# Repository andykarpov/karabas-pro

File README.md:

# Karabas-Pro

**Yet another FPGA ZX Spectrum clone ;)**

## Intro

ZX Spectrum compatible machine with a soft CPU, FDD and HDD (CF card) controllers, PS/2 keyboard/mouse, ESP8266 UART, RTC, VGA output and all logic inside the Altera FPGA **EP4CE10**.

## The idea

The idea was to make a smaller Profi (Профи) ZX Spectrum clone, with real FDD and HDD controllers. The board size fits the dimensions of the real 3.5" floppy drive. 

## Firmwares

**The main firmware is finished and currently it implements:**

1) ZX Spectrum classic and profi hi-res hi-color mode (with palette) (512x240)
2) ZX Profi CMR ports for extended peripherial
3) FDD controller that works both in CP/M and classic modes
4) HDD controller (works in Profi CP/M mode and PQ-DOS mode)
5) PS/2 keyboard (XT keyboard emulation)
6) PS/2 mouse (kempston mouse and serial MS mouse emulation)
7) VGA output (requires a monitor with 50Hz support)
8) Turbosound (2 x AY-3-8912), Soundrive and SAA1099 (SAA will work only on EP4CE10 due to lack of free LEs in EP4CE6)
9) Kempston joystick support
10) SEGA joystick support
11) RTC (profi), emulated read/write support
12) SD card access via Z-Controller emulation as well as DivMMC
13) Turbo 7 MHz (nowait) and Turbo 14 Mhz (with wait cycles)
14) ZX UNO simple UART @115200 for ESP8266 module, ZiFi API support (a secondary ZX UNO UART available on uBus connector for EP4CE10)
15) An additional ROM bank with **PQ-DOS BIOS**
16) An additional ROM bank with **Flash Tool** by **Doctor Max** to upgrade the FGPA firmware and ROM banks without programmer
17) An additional ROM bank with **FDImage Tool** by **Doctor Max** to extract TRD, SCL, PRO, TD0 and FDI images on real floppies
18) OSD menu
19) OSD full-screen overlay with easy-to-change options, RTC setup, etc.

## More info

**ERRATA for PCB rev.A:** [See ERRATA Rev.A](https://github.com/andykarpov/karabas-pro/blob/master/ERRATA-REVA.md).

**ERRATA for PCB rev.B:** [See ERRATA Rev.B](https://github.com/andykarpov/karabas-pro/blob/master/ERRATA-REVB.md).

**ERRATA for PCB rev.С:** [See ERRATA Rev.С](https://github.com/andykarpov/karabas-pro/blob/master/ERRATA-REVC.md).

**Latest stable revision:** rev.Ї.

**PCB changelog:** [PCB changelog](https://github.com/andykarpov/karabas-pro/blob/master/CHANGELOG-PCB.md).

**Profi firmware** [Download a Profi firmware](https://github.com/andykarpov/karabas-pro/tree/master/firmware/releases/profi).

**Donations** [See DONATIONS.md](https://github.com/andykarpov/karabas-pro/blob/master/DONATIONS.md).

## Development & Building

### AVR Firmware
The ATmega328P supervisor firmware is built using [PlatformIO](https://platformio.org/):

```bash
cd firmware/src/avr
pio run
```

This compiles the universal firmware, generates all revision-specific `.eep` files, and automatically syncs them to `firmware/releases/`.

To automatically rebuild and stage updated firmware binaries whenever you commit AVR changes, install the git hooks:
```bash
./scripts/install-hooks.sh
```

### Pre-production renders:

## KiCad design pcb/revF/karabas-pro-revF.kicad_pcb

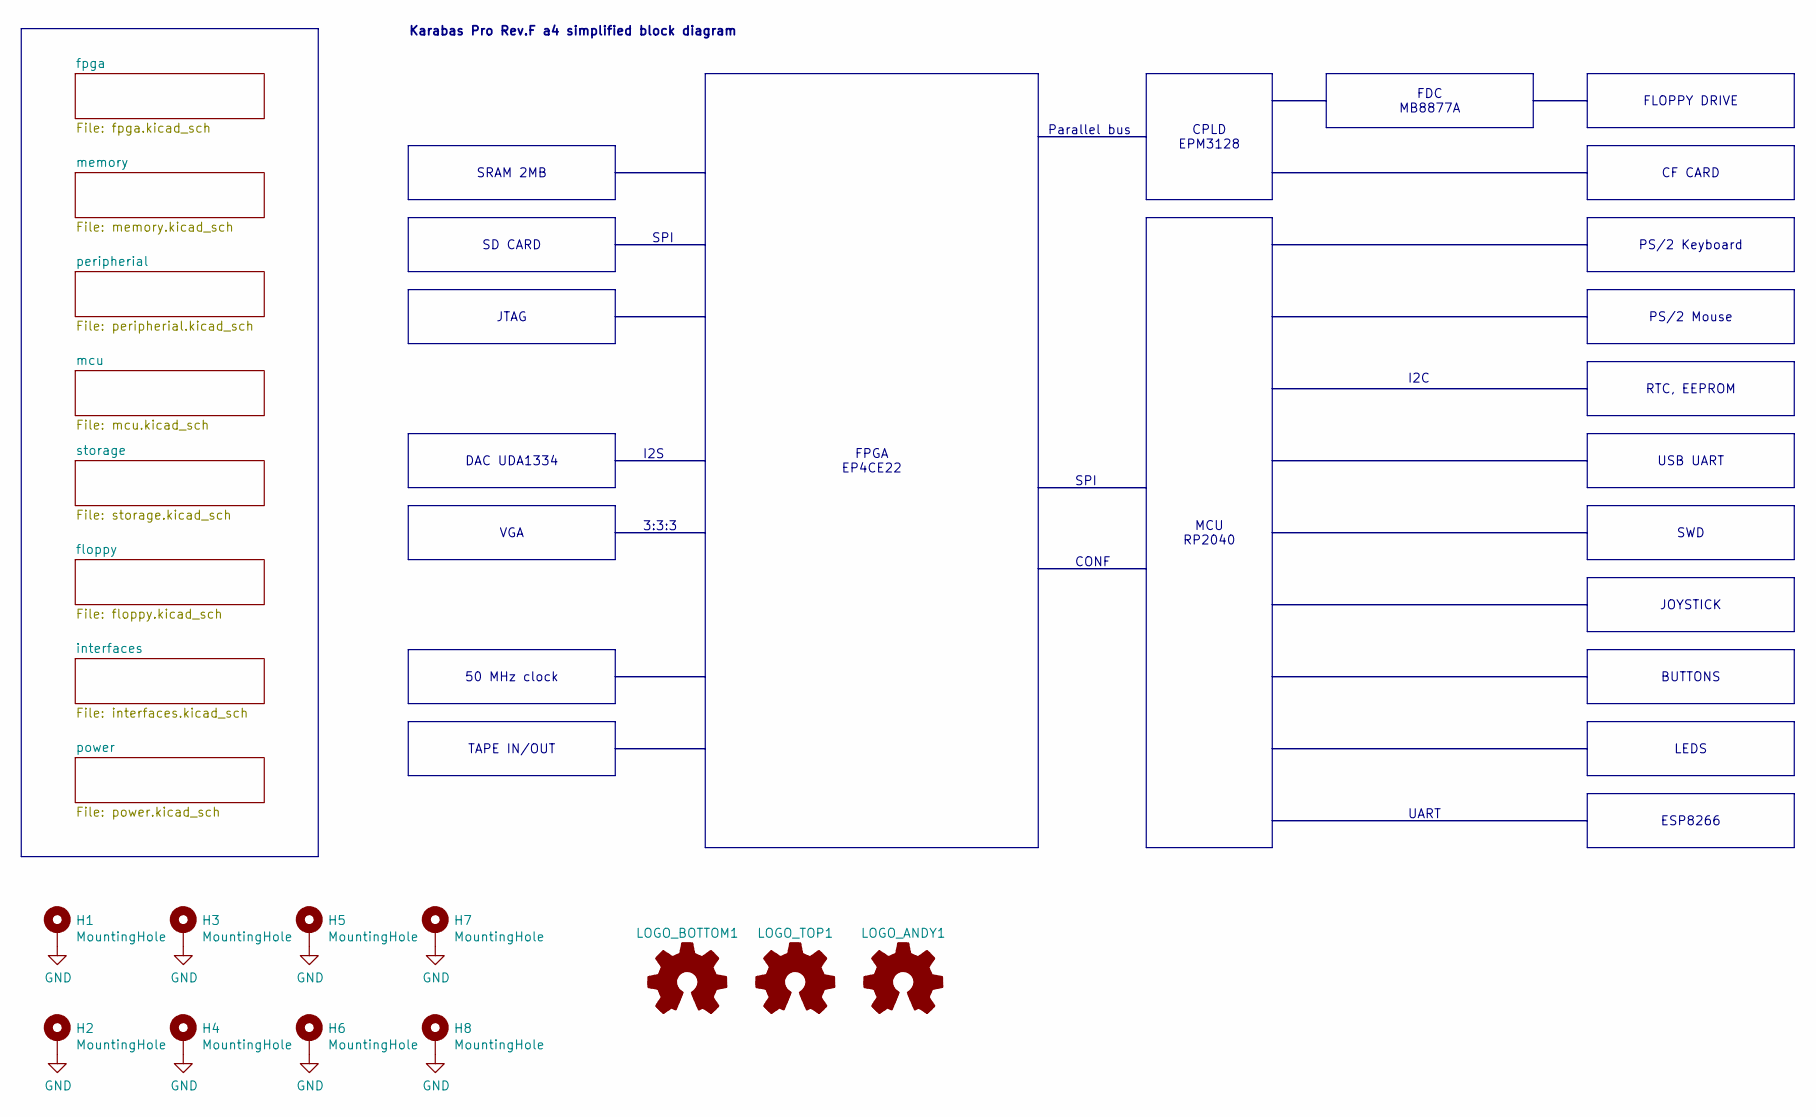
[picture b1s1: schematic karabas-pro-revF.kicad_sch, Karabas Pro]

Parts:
H1, H2, H3, H4, H5, H6, H7, H8: MountingHole; MountingHole_3.5mm_Pad_Via
LOGO_ANDY1: Logo_Open_Hardware_Small; andy_karpov_logo4_silk
LOGO_BOTTOM1: Logo_Open_Hardware_Small; karabas_pro_logo4_copper
LOGO_TOP1: Logo_Open_Hardware_Small; karabas_pro_logo4_copper

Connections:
GND: H1.1, H2.1, H3.1, H4.1, H5.1, H6.1, H7.1, H8.1; also elsewhere on the board

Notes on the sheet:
I2S
I2C
Parallel bus
3:3:3
Karabas Pro Rev.${REVISION} simplified block diagram
UART
SPI
CONF
PS/2 Keyboard
FDC MB8877A
CPLD EPM3128
50 MHz clock
JTAG
RTC, EEPROM
ESP8266
BUTTONS
PS/2 Mouse
USB UART
JOYSTICK
SWD
CF CARD
VGA
SD CARD
TAPE IN/OUT
SRAM 2MB
LEDS
FLOPPY DRIVE
FPGA EP4CE22
DAC UDA1334
MCU RP2040

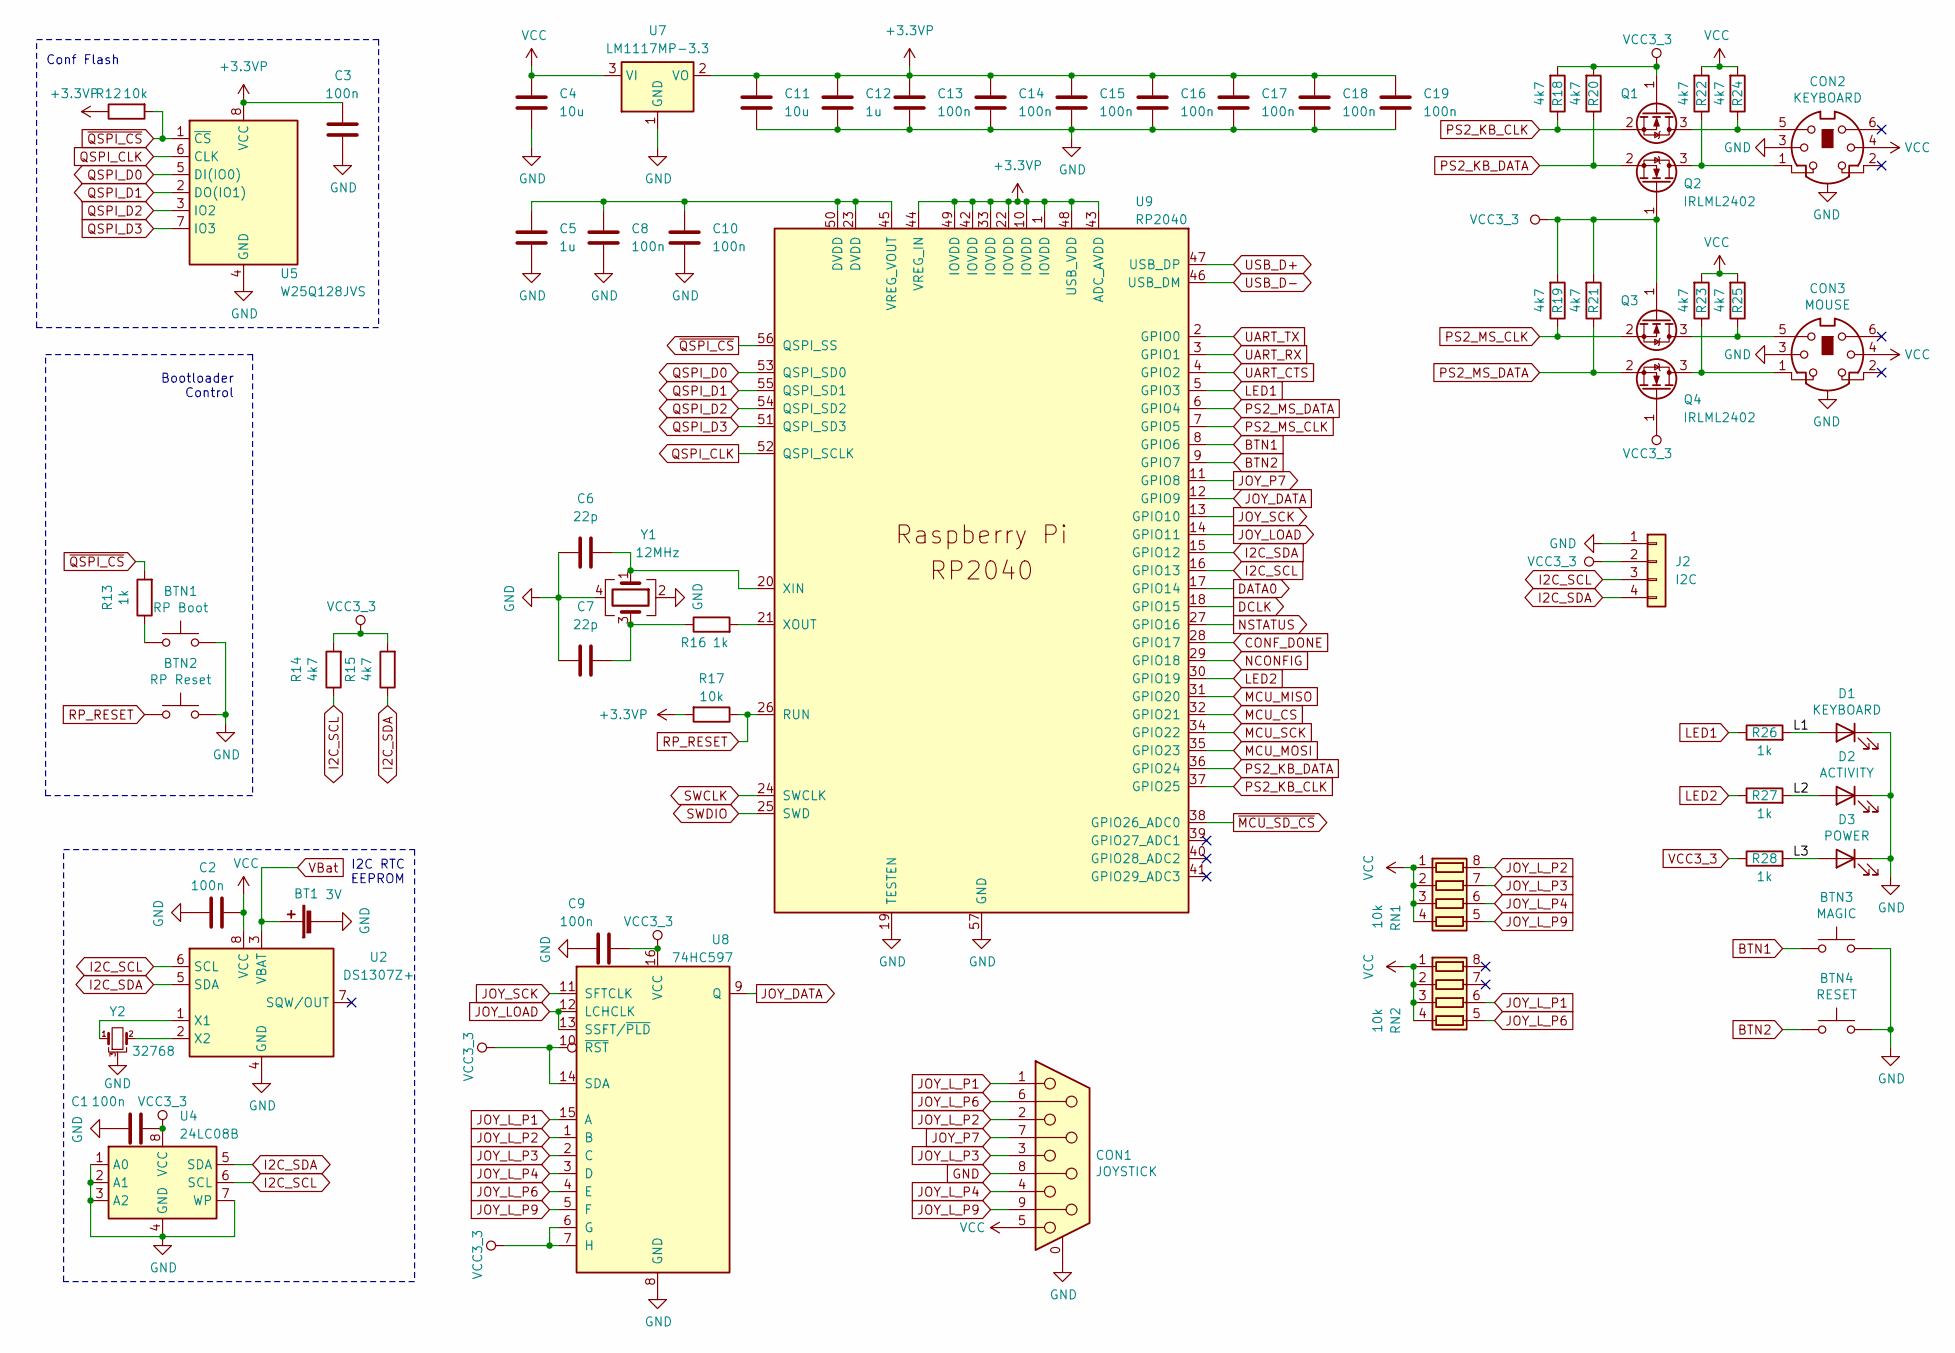
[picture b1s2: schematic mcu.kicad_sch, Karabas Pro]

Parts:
BT1: 3V; BAT_BS-7-BLUE
BTN1: RP Boot; SW_SPST_PTS810_handsoldering
BTN2: RP Reset; SW_SPST_PTS810_handsoldering
BTN3: MAGIC; SW_Tactile_SPST_Angled_PTS645Vx58-2LFS
BTN4: RESET; SW_Tactile_SPST_Angled_PTS645Vx58-2LFS
C1, C2, C3, C8, C9, C10, C13, C14, C15, C16, C17, C18, C19: 100n; C_0805_2012Metric_Pad1.18x1.45mm_HandSolder
C4, C11: 10u; C_0805_2012Metric_Pad1.18x1.45mm_HandSolder
C5, C12: 1u; C_0805_2012Metric_Pad1.18x1.45mm_HandSolder
C6, C7: 22p; C_0805_2012Metric_Pad1.18x1.45mm_HandSolder
CON1: JOYSTICK; DSUB-9_Pins_Horizontal_P2.77x2.84mm_EdgePinOffset7.70mm_Hou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
CON2: KEYBOARD; MINI_DIN_6_33PRIMARY
CON3: MOUSE; MINI_DIN_6_33PRIMARY
D1: KEYBOARD; LED_0805_2012Metric_Pad1.15x1.40mm_HandSolder
D2: ACTIVITY; LED_0805_2012Metric_Pad1.15x1.40mm_HandSolder
D3: POWER; LED_0805_2012Metric_Pad1.15x1.40mm_HandSolder
J2: I2C; PinHeader_1x04_P2.54mm_Vertical
Q1, Q2, Q3, Q4: IRLML2402; SOT-23_Handsoldering
R12, R17: 10k; R_0805_2012Metric_Pad1.20x1.40mm_HandSolder
R13, R16, R26, R27, R28: 1k; R_0805_2012Metric_Pad1.20x1.40mm_HandSolder
R14, R15, R18, R19, R20, R21, R22, R23, R24, R25: 4k7; R_0805_2012Metric_Pad1.20x1.40mm_HandSolder
RN1, RN2: 10k; R_Array_Convex_4x0603
U2: DS1307Z+; SOIC-8_3.9x4.9mm_P1.27mm
U4: 24LC08B; SO-8_3.9x4.9mm_P1.27mm
U5: W25Q128JVS; SOIC-8_5.23x5.23mm_P1.27mm-LONG
U7: LM1117MP-3.3; SOT-223-3_TabPin2
U8: 74HC597; SO-16_3.9x9.9mm_P1.27mm
U9: RP2040; QFN-56-1EP_7x7mm_P0.4mm_EP3.2x3.2mm_ThermalViaBig
Y1: 12MHz; Crystal_SMD_3225-4Pin_3.2x2.5mm_HandSoldering
Y2: 32768; Crystal_C26-LF_D2.1mm_L6.5mm_Horizontal_1EP_style2

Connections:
+3.3VP: C3.2, C11.1, C12.1, C13.1, C14.1, C15.1, C16.1, C17.1, C18.1, C19.1, R12.1, R17.2, U5.8 (VCC), U7.2 (VO), U9.1 (IOVDD), U9.10 (IOVDD), U9.22 (IOVDD), U9.33 (IOVDD), U9.42 (IOVDD), U9.43 (ADC_AVDD), U9.44 (VREG_IN), U9.48 (USB_VDD), U9.49 (IOVDD)
/mcu/L1: D1.2 (A), R26.2
/mcu/L2: D2.2 (A), R27.2
/mcu/L3: D3.2 (A), R28.2
BTN1: BTN3.1, U9.8 (GPIO6)
BTN2: BTN4.1, U9.9 (GPIO7)
CONF_DONE: U9.28 (GPIO17); also elsewhere on the board
DATA0: U9.17 (GPIO14); also elsewhere on the board
DCLK: U9.18 (GPIO15); also elsewhere on the board
GND: BT1.2 (-), BTN1.2, BTN2.2, BTN3.2, BTN4.2, C1.2, C2.2, C3.1, C4.2, C5.2, C6.2, C7.2, C8.2, C9.2, C10.2, C11.2, C12.2, C13.2, C14.2, C15.2, C16.2, C17.2, C18.2, C19.2, CON1.0 (PAD), CON1.8, CON2.3, CON2.GND, CON3.3, CON3.GND, D1.1 (K), D2.1 (K), D3.1 (K), J2.1, U2.4 (GND), U4.1 (A0), U4.2 (A1), U4.3 (A2), U4.4 (GND), U4.7 (WP), U5.4 (GND), U7.1 (GND), U8.8 (GND), U9.19 (TESTEN), U9.57 (GND), Y1.2, Y1.4, Y2.3; also elsewhere on the board
I2C_SCL: J2.3, R14.1, U2.6 (SCL), U4.6 (SCL), U9.16 (GPIO13)
I2C_SDA: J2.4, R15.1, U2.5 (SDA), U4.5 (SDA), U9.15 (GPIO12)
JOY_DATA: U8.9 (Q), U9.12 (GPIO9)
JOY_LOAD: U8.12 (LCHCLK), U8.13 (SSFT/~PLD), U9.14 (GPIO11)
JOY_L_P1: CON1.1, RN2.6 (R3.2), U8.15 (A)
JOY_L_P2: CON1.2, RN1.8 (R1.2), U8.1 (B)
JOY_L_P3: CON1.3, RN1.7 (R2.2), U8.2 (C)
JOY_L_P4: CON1.4, RN1.6 (R3.2), U8.3 (D)
JOY_L_P6: CON1.6, RN2.5 (R4.2), U8.4 (E)
JOY_L_P9: CON1.9, RN1.5 (R4.2), U8.5 (F)
JOY_P7: CON1.7, U9.11 (GPIO8)
JOY_SCK: U8.11 (SFTCLK), U9.13 (GPIO10)
LED1: R26.1, U9.5 (GPIO3)
LED2: R27.1, U9.30 (GPIO19)
MCU_CS: U9.32 (GPIO21); also elsewhere on the board
MCU_MISO: U9.31 (GPIO20); also elsewhere on the board
MCU_MOSI: U9.35 (GPIO23); also elsewhere on the board
MCU_SCK: U9.34 (GPIO22); also elsewhere on the board
NCONFIG: U9.29 (GPIO18); also elsewhere on the board
NSTATUS: U9.27 (GPIO16); also elsewhere on the board
unnamed: BTN1.1, R13.1
unnamed: C7.1, R16.1, Y1.3
unnamed: CON2.5, Q1.3 (D), R24.1
unnamed: CON2.1, Q2.3 (D), R22.1
unnamed: CON3.5, Q3.3 (D), R25.1
unnamed: CON3.1, Q4.3 (D), R23.1
unnamed: U2.1 (X1), Y2.1
unnamed: U2.2 (X2), Y2.2
unnamed: C5.1, C8.1, C10.1, U9.23 (DVDD), U9.45 (VREG_VOUT), U9.50 (DVDD)
unnamed: C6.1, U9.20 (XIN), Y1.1
unnamed: R16.2, U9.21 (XOUT)
PS2_KB_CLK: Q1.2 (S), R18.1, U9.37 (GPIO25)
PS2_KB_DATA: Q2.2 (S), R20.1, U9.36 (GPIO24)
PS2_MS_CLK: Q3.2 (S), R19.1, U9.7 (GPIO5)
PS2_MS_DATA: Q4.2 (S), R21.1, U9.6 (GPIO4)
QSPI_CLK: U5.6 (CLK), U9.52 (QSPI_SCLK)
QSPI_D0: U5.5 (DI(IO0)), U9.53 (QSPI_SD0)
QSPI_D1: U5.2 (DO(IO1)), U9.55 (QSPI_SD1)
QSPI_D2: U5.3 (IO2), U9.54 (QSPI_SD2)
QSPI_D3: U5.7 (IO3), U9.51 (QSPI_SD3)
RP_RESET: BTN2.1, R17.1, U9.26 (RUN)
SWCLK: U9.24 (SWCLK)
SWDIO: U9.25 (SWD)
UART_CTS: U9.4 (GPIO2); also elsewhere on the board
UART_RX: U9.3 (GPIO1); also elsewhere on the board
UART_TX: U9.2 (GPIO0); also elsewhere on the board
USB_D+: U9.47 (USB_DP); also elsewhere on the board
USB_D-: U9.46 (USB_DM); also elsewhere on the board
VBat: BT1.1 (+), U2.3 (VBAT)
VCC: C2.1, C4.1, CON1.5, CON2.4, CON3.4, R22.2, R23.2, R24.2, R25.2, RN1.1 (R1.1), RN1.2 (R2.1), RN1.3 (R3.1), RN1.4 (R4.1), RN2.1 (R1.1), RN2.2 (R2.1), RN2.3 (R3.1), RN2.4 (R4.1), U2.8 (VCC), U7.3 (VI); also elsewhere on the board
VCC3_3: C1.1, C9.1, J2.2, Q1.1 (G), Q2.1 (G), Q3.1 (G), Q4.1 (G), R14.2, R15.2, R18.2, R19.2, R20.2, R21.2, R28.1, U4.8 (VCC), U8.6 (G), U8.7 (H), U8.10 (~RST), U8.14 (SDA), U8.16 (VCC); also elsewhere on the board
~MCU_SD_CS: U9.38 (GPIO26_ADC0); also elsewhere on the board
~QSPI_CS: R12.2, R13.2, U5.1 (~CS), U9.56 (QSPI_SS)

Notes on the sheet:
I2C RTC EEPROM
Bootloader Control
Conf Flash

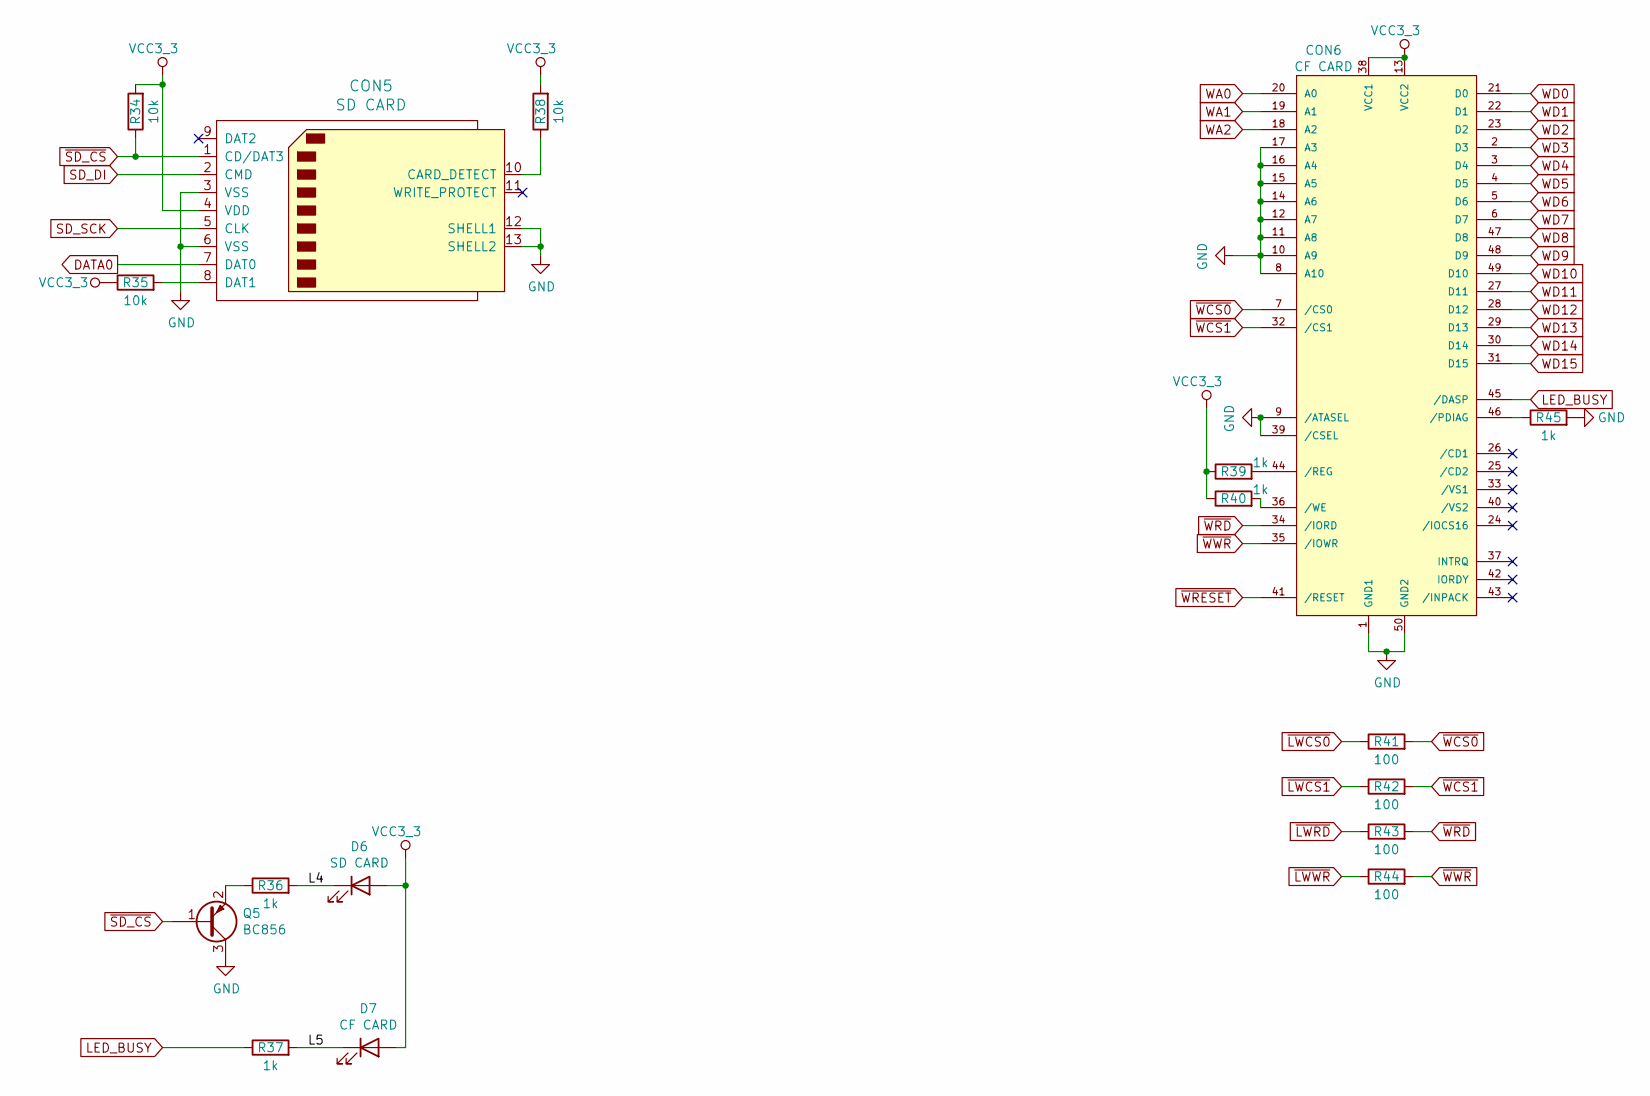
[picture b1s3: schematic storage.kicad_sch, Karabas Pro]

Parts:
CON5: SD CARD; SD_TE_2041021-mod
CON6: CF CARD; TE_1734451-1-LONG
D6: SD CARD; LED_0805_2012Metric_Pad1.15x1.40mm_HandSolder
D7: CF CARD; LED_0805_2012Metric_Pad1.15x1.40mm_HandSolder
Q5: BC856; SOT-23_Handsoldering
R34, R35, R38: 10k; R_0805_2012Metric_Pad1.20x1.40mm_HandSolder
R36, R37, R39, R40, R45: 1k; R_0805_2012Metric_Pad1.20x1.40mm_HandSolder
R41, R42, R43, R44: 100; R_0805_2012Metric_Pad1.20x1.40mm_HandSolder

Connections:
/storage/L4: D6.1 (K), R36.2
/storage/L5: D7.1 (K), R37.2
DATA0: CON5.7 (DAT0); also elsewhere on the board
GND: CON5.3 (VSS), CON5.6 (VSS), CON5.12 (SHELL1), CON5.13 (SHELL2), CON6.1 (GND1), CON6.8 (A10), CON6.9 (/ATASEL), CON6.10 (A9), CON6.11 (A8), CON6.12 (A7), CON6.14 (A6), CON6.15 (A5), CON6.16 (A4), CON6.17 (A3), CON6.39 (/CSEL), CON6.50 (GND2), Q5.3 (C), R45.2; also elsewhere on the board
LED_BUSY: CON6.45 (/DASP), R37.1
unnamed: CON5.10 (CARD_DETECT), R38.1
unnamed: CON5.8 (DAT1), R35.2
unnamed: CON6.46 (/PDIAG), R45.1
unnamed: CON6.44 (/REG), R39.2
unnamed: CON6.36 (/WE), R40.2
unnamed: Q5.2 (E), R36.1
SD_DI: CON5.2 (CMD); also elsewhere on the board
SD_SCK: CON5.5 (CLK); also elsewhere on the board
VCC3_3: CON5.4 (VDD), CON6.13 (VCC2), CON6.38 (VCC1), D6.2 (A), D7.2 (A), R34.2, R35.1, R38.2, R39.1, R40.1; also elsewhere on the board
WA0: CON6.20 (A0); also elsewhere on the board
WA1: CON6.19 (A1); also elsewhere on the board
WA2: CON6.18 (A2); also elsewhere on the board
WD0: CON6.21 (D0); also elsewhere on the board
WD1: CON6.22 (D1); also elsewhere on the board
WD2: CON6.23 (D2); also elsewhere on the board
WD3: CON6.2 (D3); also elsewhere on the board
WD4: CON6.3 (D4); also elsewhere on the board
WD5: CON6.4 (D5); also elsewhere on the board
WD6: CON6.5 (D6); also elsewhere on the board
WD7: CON6.6 (D7); also elsewhere on the board
WD8: CON6.47 (D8); also elsewhere on the board
WD9: CON6.48 (D9); also elsewhere on the board
WD10: CON6.49 (D10); also elsewhere on the board
WD11: CON6.27 (D11); also elsewhere on the board
WD12: CON6.28 (D12); also elsewhere on the board
WD13: CON6.29 (D13); also elsewhere on the board
WD14: CON6.30 (D14); also elsewhere on the board
WD15: CON6.31 (D15); also elsewhere on the board
~LWCS0: R41.1; also elsewhere on the board
~LWCS1: R42.1; also elsewhere on the board
~LWRD: R43.1; also elsewhere on the board
~LWWR: R44.1; also elsewhere on the board
~SD_CS: CON5.1 (CD/DAT3), Q5.1 (B), R34.1; also elsewhere on the board
~WCS0: CON6.7 (/CS0), R41.2
~WCS1: CON6.32 (/CS1), R42.2
~WRD: CON6.34 (/IORD), R43.2
~WRESET: CON6.41 (/RESET); also elsewhere on the board
~WWR: CON6.35 (/IOWR), R44.2

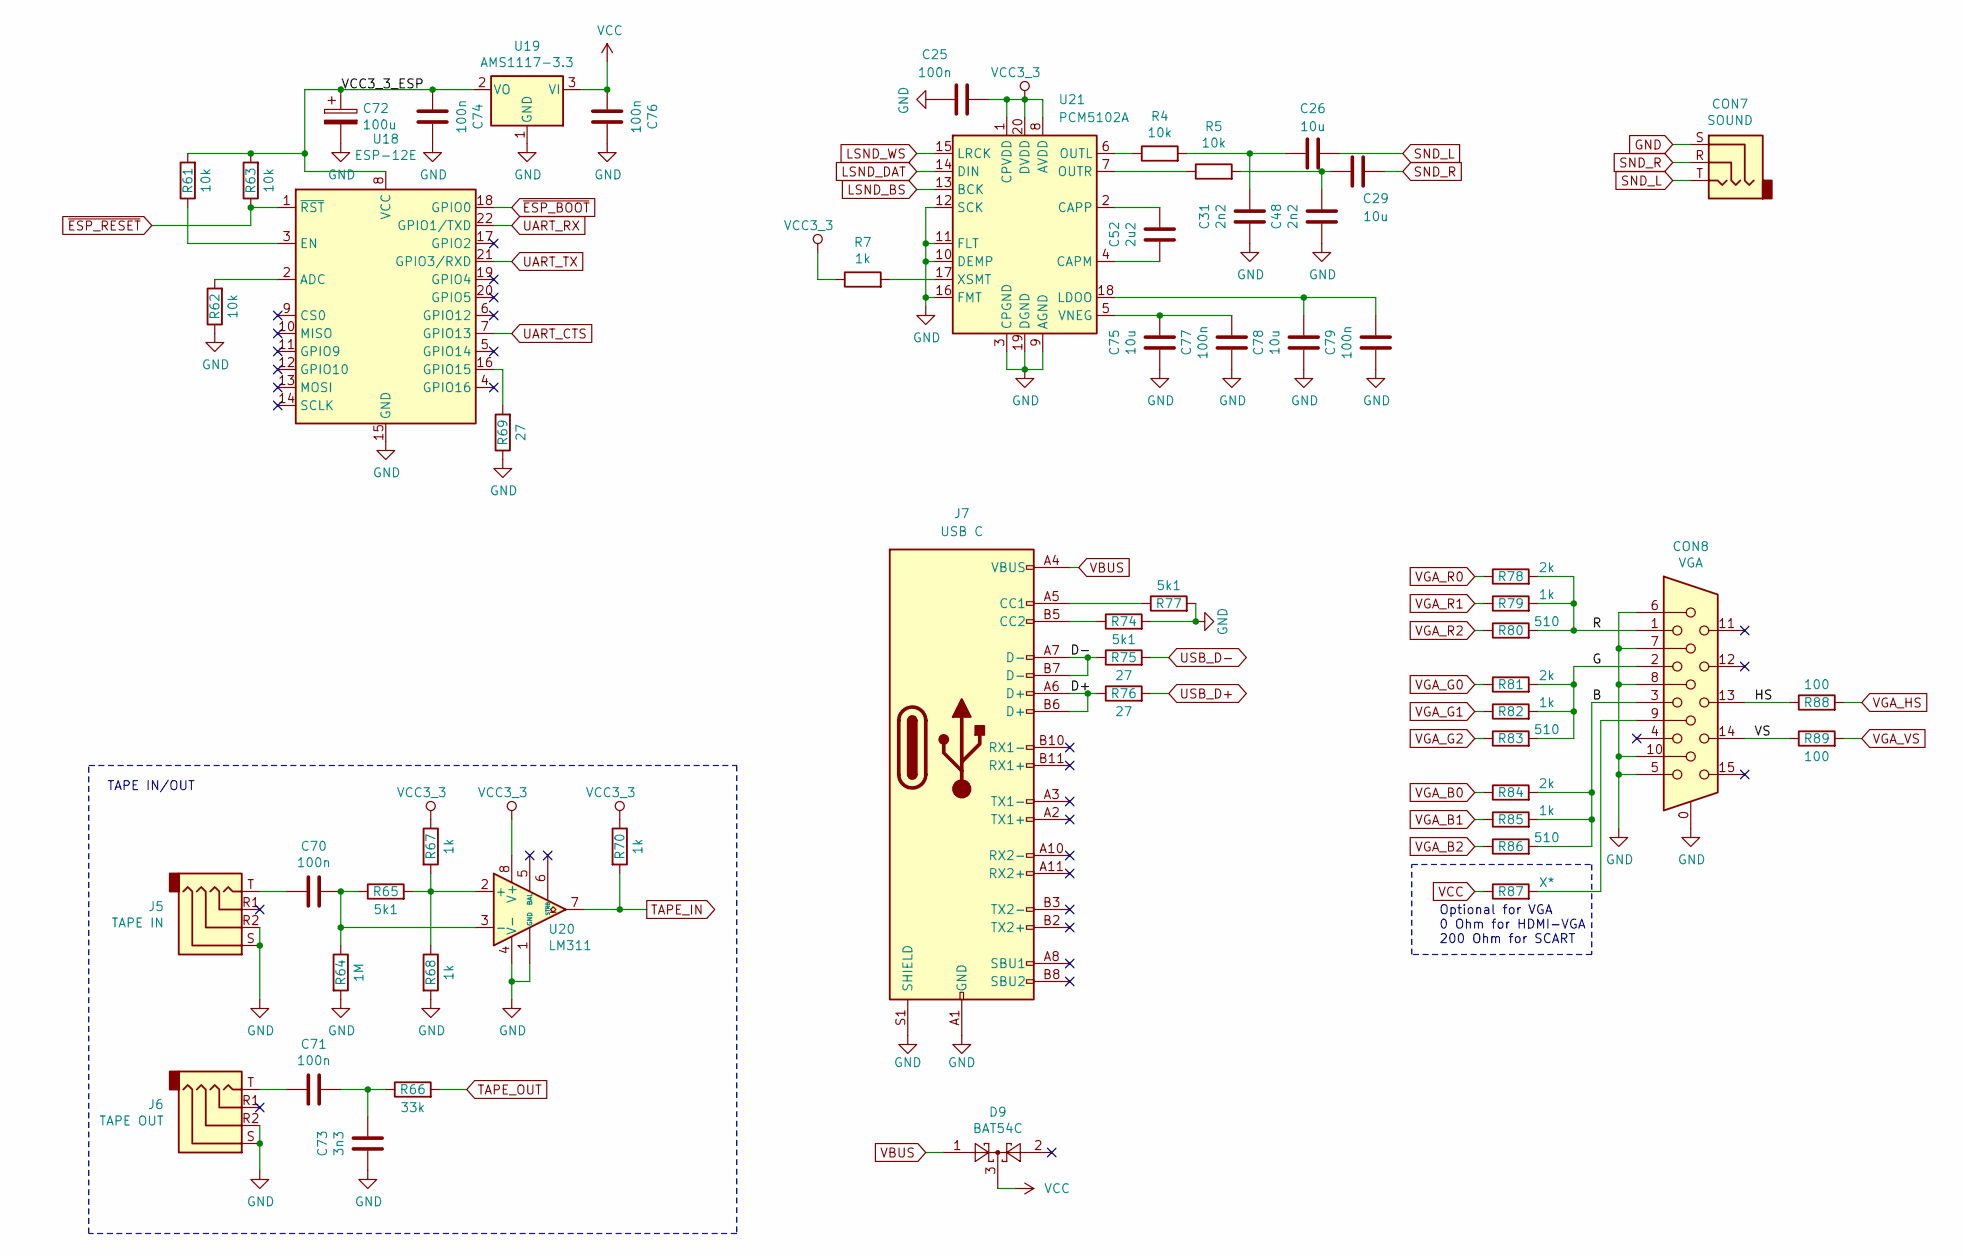
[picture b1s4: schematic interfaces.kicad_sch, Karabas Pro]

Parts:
C25, C70, C71, C74, C76, C77, C79: 100n; C_0805_2012Metric_Pad1.18x1.45mm_HandSolder
C26, C29, C75, C78: 10u; C_0805_2012Metric_Pad1.18x1.45mm_HandSolder
C31, C48: 2n2; C_0805_2012Metric_Pad1.18x1.45mm_HandSolder
C52: 2u2; C_0805_2012Metric_Pad1.18x1.45mm_HandSolder
C72: 100u; CP_EIA-7343-31_Kemet-D-uni
C73: 3n3; C_0805_2012Metric_Pad1.18x1.45mm_HandSolder
CON7: SOUND; Jack_3.5mm_CUI_SJ1-3535NG_Horizontal
CON8: VGA; DSUB-15-HD_Socket_Horizontal_P2.29x1.90mm_EdgePinOffset3.03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
D9: BAT54C; SOT-23_Handsoldering
J5: TAPE IN; AUDIO_JACK_3.5MM_SMD_TRRS_rounded_mixed
J6: TAPE OUT; AUDIO_JACK_3.5MM_SMD_TRRS_rounded_mixed
J7: USB C; USB_C_Receptacle_XKB_U262-16XN-4BVC11
R4, R5, R61, R62, R63: 10k; R_0805_2012Metric_Pad1.20x1.40mm_HandSolder
R7, R67, R68, R70, R79, R82, R85: 1k; R_0805_2012Metric_Pad1.20x1.40mm_HandSolder
R64: 1M; R_0805_2012Metric_Pad1.20x1.40mm_HandSolder
R65, R74, R77: 5k1; R_0805_2012Metric_Pad1.20x1.40mm_HandSolder
R66: 33k; R_0805_2012Metric_Pad1.20x1.40mm_HandSolder
R69, R75, R76: 27; R_0805_2012Metric_Pad1.20x1.40mm_HandSolder
R78, R81, R84: 2k; R_0805_2012Metric_Pad1.20x1.40mm_HandSolder
R80, R83, R86: 510; R_0805_2012Metric_Pad1.20x1.40mm_HandSolder
R87: X*; R_0805_2012Metric_Pad1.20x1.40mm_HandSolder
R88, R89: 100; R_0805_2012Metric_Pad1.20x1.40mm_HandSolder
U18: ESP-12E
U19: AMS1117-3.3; SOT-223-3_TabPin2
U20: LM311; SO-8_3.9x4.9mm_P1.27mm
U21: PCM5102A; TSSOP-20_4.4x6.5mm_P0.65mm

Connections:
/interfaces/B: CON8.3, R84.2, R85.2, R86.2
/interfaces/D+: J7.A6 (D+), J7.B6 (D+), R76.1
/interfaces/D-: J7.A7 (D-), J7.B7 (D-), R75.1
/interfaces/G: CON8.2, R81.2, R82.2, R83.2
/interfaces/HS: CON8.13, R88.1
/interfaces/R: CON8.1, R78.2, R79.2, R80.2
/interfaces/VCC3_3_ESP: C72.1, C74.1, R61.2, R63.2, U18.8 (VCC), U19.2 (VO)
/interfaces/VS: CON8.14, R89.1
GND: C25.2, C31.1, C48.1, C72.2, C73.1, C74.2, C75.1, C76.2, C77.1, C78.1, C79.1, CON7.S, CON8.0, CON8.5, CON8.6, CON8.7, CON8.8, CON8.10, J5.R2, J5.S, J6.R2, J6.S, J7.A1 (GND), J7.A12 (GND), J7.B1 (GND), J7.B12 (GND), J7.S1 (SHIELD), R62.1, R64.2, R68.2, R69.1, R74.2, R77.2, U18.15 (GND), U19.1 (GND), U20.1 (GND), U20.4 (V-), U21.3 (CPGND), U21.9 (AGND), U21.10 (DEMP), U21.11 (FLT), U21.12 (SCK), U21.16 (FMT), U21.19 (DGND); also elsewhere on the board
LSND_BS: U21.13 (BCK); also elsewhere on the board
LSND_DAT: U21.14 (DIN); also elsewhere on the board
LSND_WS: U21.15 (LRCK); also elsewhere on the board
unnamed: C26.2, C31.2, R4.2
unnamed: C29.2, C48.2, R5.2
unnamed: C70.1, J5.T
unnamed: C71.1, J6.T
unnamed: C71.2, C73.2, R66.1
unnamed: CON8.9, R87.2
unnamed: J7.A5 (CC1), R77.1
unnamed: J7.B5 (CC2), R74.1
unnamed: R62.2, U18.2 (ADC)
unnamed: R61.1, U18.3 (EN)
unnamed: R69.2, U18.16 (GPIO15)
unnamed: R65.2, R67.2, R68.1, U20.2 (+)
unnamed: C70.2, R64.1, R65.1, U20.3 (-)
unnamed: C52.1, U21.4 (CAPM)
unnamed: C52.2, U21.2 (CAPP)
unnamed: C78.2, C79.2, U21.18 (LDOO)
unnamed: R4.1, U21.6 (OUTL)
unnamed: R5.1, U21.7 (OUTR)
unnamed: C75.2, C77.2, U21.5 (VNEG)
unnamed: R7.2, U21.17 (XSMT)
SND_L: C26.1, CON7.T
SND_R: C29.1, CON7.R
TAPE_IN: R70.2, U20.7; also elsewhere on the board
TAPE_OUT: R66.2; also elsewhere on the board
UART_CTS: U18.7 (GPIO13); also elsewhere on the board
UART_RX: U18.22 (GPIO1/TXD); also elsewhere on the board
UART_TX: U18.21 (GPIO3/RXD); also elsewhere on the board
USB_D+: R76.2; also elsewhere on the board
USB_D-: R75.2; also elsewhere on the board
VBUS: D9.1, J7.A4 (VBUS), J7.A9 (VBUS), J7.B4 (VBUS), J7.B9 (VBUS)
VCC: C76.1, D9.3, R87.1, U19.3 (VI); also elsewhere on the board
VCC3_3: C25.1, R7.1, R67.1, R70.1, U20.8 (V+), U21.1 (CPVDD), U21.8 (AVDD), U21.20 (DVDD); also elsewhere on the board
VGA_B0: R84.1; also elsewhere on the board
VGA_B1: R85.1; also elsewhere on the board
VGA_B2: R86.1; also elsewhere on the board
VGA_G0: R81.1; also elsewhere on the board
VGA_G1: R82.1; also elsewhere on the board
VGA_G2: R83.1; also elsewhere on the board
VGA_HS: R88.2; also elsewhere on the board
VGA_R0: R78.1; also elsewhere on the board
VGA_R1: R79.1; also elsewhere on the board
VGA_R2: R80.1; also elsewhere on the board
VGA_VS: R89.2; also elsewhere on the board
~ESP_BOOT: U18.18 (GPIO0)
~ESP_RESET: R63.1, U18.1 (~RST)

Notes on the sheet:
Optional for VGA 0 Ohm for HDMI-VGA 200 Ohm for SCART
TAPE IN/OUT

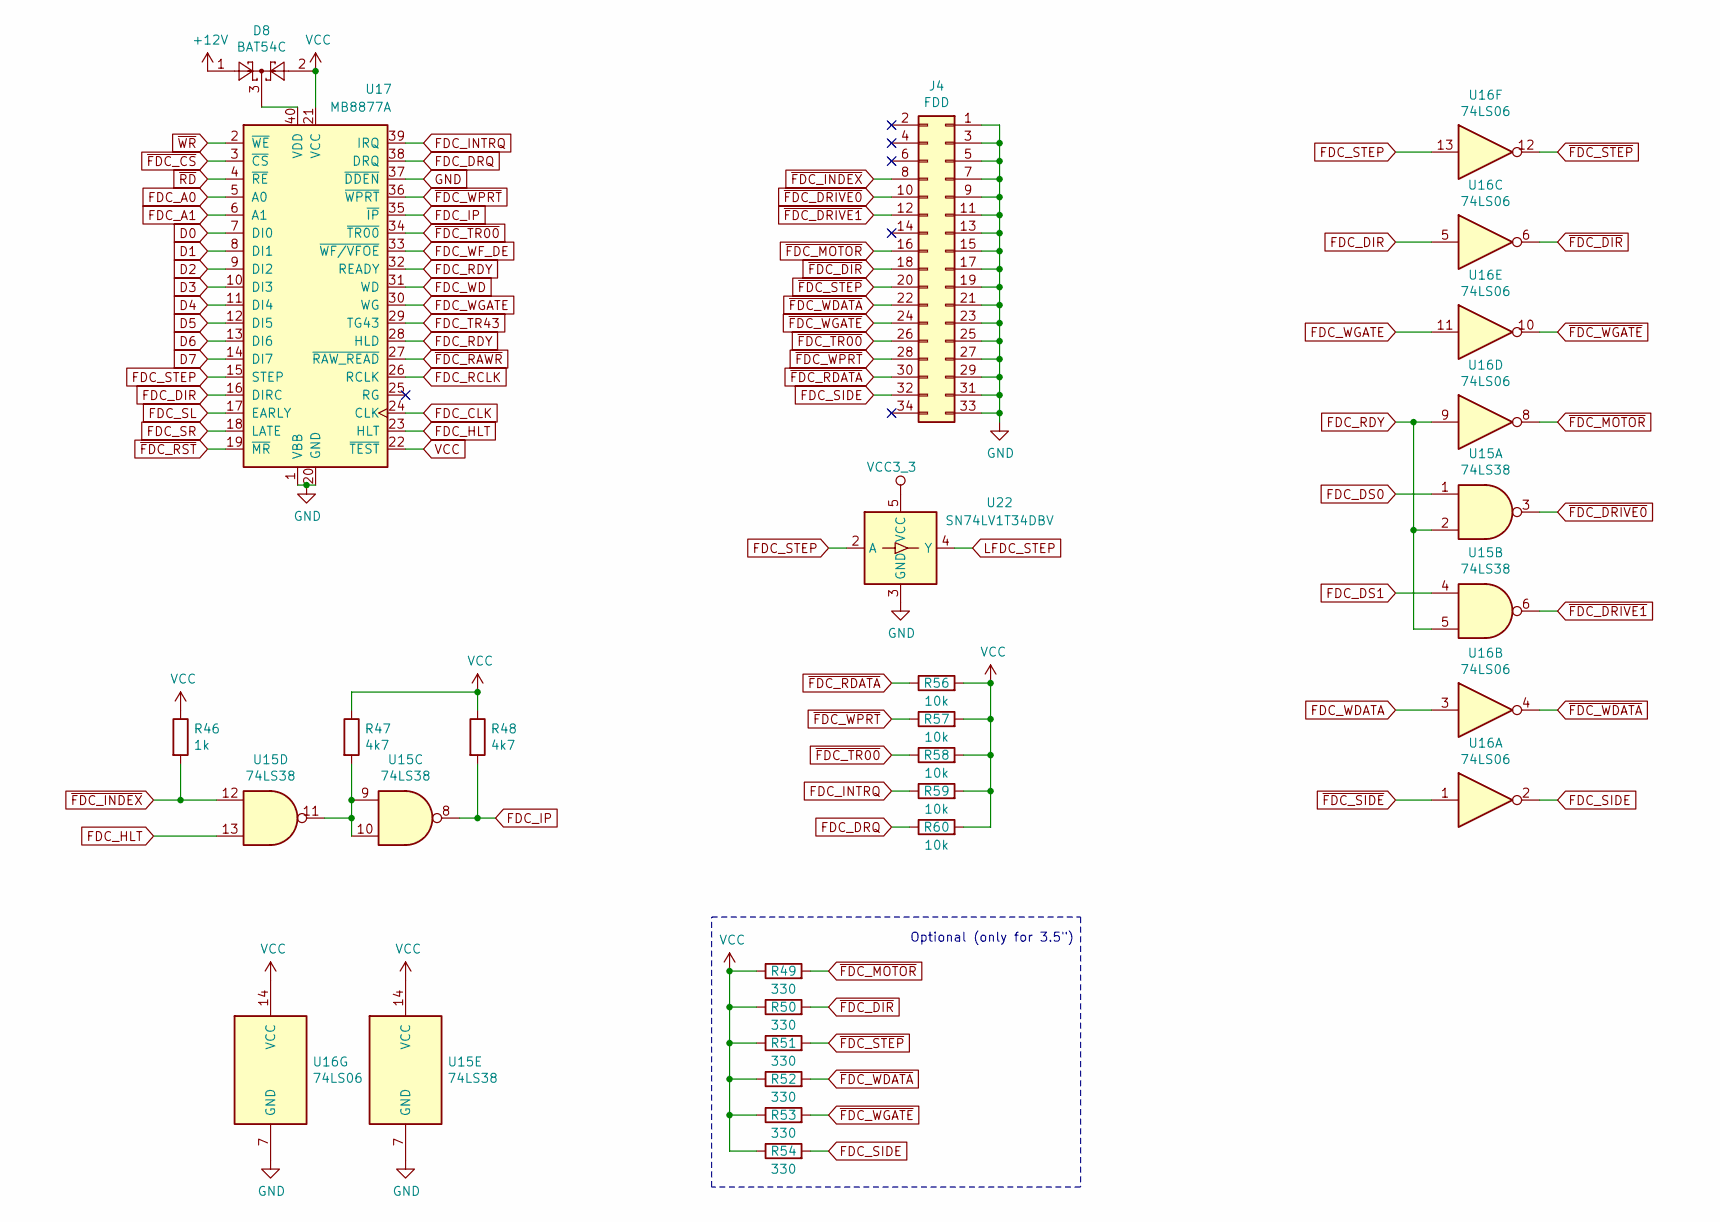
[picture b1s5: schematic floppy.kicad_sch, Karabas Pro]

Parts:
D8: BAT54C; SOT-23_Handsoldering
J4: FDD; IDC-Header_2x17_P2.54mm_Vertical
R46: 1k; R_0805_2012Metric_Pad1.20x1.40mm_HandSolder
R47, R48: 4k7; R_0805_2012Metric_Pad1.20x1.40mm_HandSolder
R49, R50, R51, R52, R53, R54: 330; R_0805_2012Metric_Pad1.20x1.40mm_HandSolder
R56, R57, R58, R59, R60: 10k; R_0805_2012Metric_Pad1.20x1.40mm_HandSolder
U15: 74LS38; DIP-14_W7.62mm
U16: 74LS06; DIP-14_W7.62mm
U17: MB8877A; DIP-40_W15.24mm
U22: SN74LV1T34DBV; SOT-23-5

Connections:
+12V: D8.1; also elsewhere on the board
D0: U17.7 (DI0); also elsewhere on the board
D1: U17.8 (DI1); also elsewhere on the board
D2: U17.9 (DI2); also elsewhere on the board
D3: U17.10 (DI3); also elsewhere on the board
D4: U17.11 (DI4); also elsewhere on the board
D5: U17.12 (DI5); also elsewhere on the board
D6: U17.13 (DI6); also elsewhere on the board
D7: U17.14 (DI7); also elsewhere on the board
FDC_A0: U17.5 (A0); also elsewhere on the board
FDC_A1: U17.6 (A1); also elsewhere on the board
FDC_CLK: U17.24 (CLK); also elsewhere on the board
FDC_DIR: U16.5, U17.16 (DIRC)
FDC_DRQ: R60.1, U17.38 (DRQ); also elsewhere on the board
FDC_DS0: U15.1; also elsewhere on the board
FDC_DS1: U15.4; also elsewhere on the board
FDC_HLT: U15.13, U17.23 (HLT); also elsewhere on the board
FDC_INTRQ: R59.1, U17.39 (IRQ); also elsewhere on the board
FDC_IP: R48.2, U15.8, U17.35 (~IP)
FDC_RCLK: U17.26 (RCLK); also elsewhere on the board
FDC_RDY: U15.2, U15.5, U16.9, U17.28 (HLD), U17.32 (READY)
FDC_SIDE: J4.32, R54.2, U16.2
FDC_SL: U17.17 (EARLY); also elsewhere on the board
FDC_SR: U17.18 (LATE); also elsewhere on the board
FDC_STEP: U16.13, U17.15 (STEP), U22.2 (A)
FDC_TR43: U17.29 (TG43); also elsewhere on the board
FDC_WD: U17.31 (WD); also elsewhere on the board
FDC_WDATA: U16.3; also elsewhere on the board
FDC_WF_DE: U17.33 (~WF/VFOE); also elsewhere on the board
FDC_WGATE: U16.11, U17.30 (WG)
GND: J4.1, J4.3, J4.5, J4.7, J4.9, J4.11, J4.13, J4.15, J4.17, J4.19, J4.21, J4.23, J4.25, J4.27, J4.29, J4.31, J4.33, U15.7 (GND), U16.7 (GND), U17.1 (VBB), U17.20 (GND), U17.37 (~DDEN), U22.3 (GND); also elsewhere on the board
LFDC_STEP: U22.4 (Y); also elsewhere on the board
unnamed: R47.2, U15.9, U15.10, U15.11
unnamed: D8.3, U17.40 (VDD)
VCC: D8.2, R46.1, R47.1, R48.1, R49.1, R50.1, R51.1, R52.1, R53.1, R54.1, R56.2, R57.2, R58.2, R59.2, R60.2, U15.14 (VCC), U16.14 (VCC), U17.21 (VCC), U17.22 (~TEST); also elsewhere on the board
VCC3_3: U22.5 (VCC); also elsewhere on the board
~FDC_CS: U17.3 (~CS); also elsewhere on the board
~FDC_DIR: J4.18, R50.2, U16.6
~FDC_DRIVE0: J4.10, U15.3
~FDC_DRIVE1: J4.12, U15.6
~FDC_INDEX: J4.8, R46.2, U15.12
~FDC_MOTOR: J4.16, R49.2, U16.8
~FDC_RAWR: U17.27 (~RAW_READ); also elsewhere on the board
~FDC_RDATA: J4.30, R56.1; also elsewhere on the board
~FDC_RST: U17.19 (~MR); also elsewhere on the board
~FDC_SIDE: U16.1; also elsewhere on the board
~FDC_STEP: J4.20, R51.2, U16.12
~FDC_TR00: J4.26, R58.1, U17.34 (~TR00)
~FDC_WDATA: J4.22, R52.2, U16.4
~FDC_WGATE: J4.24, R53.2, U16.10
~FDC_WPRT: J4.28, R57.1, U17.36 (~WPRT)
~RD: U17.4 (~RE); also elsewhere on the board
~WR: U17.2 (~WE); also elsewhere on the board

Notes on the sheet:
Optional (only for 3.5")

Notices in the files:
pcb/revE/karabas-pro-revE.kicad_pcb:
© 2021
pcb/revF/karabas-pro-revF.kicad_pcb:
© 2026
